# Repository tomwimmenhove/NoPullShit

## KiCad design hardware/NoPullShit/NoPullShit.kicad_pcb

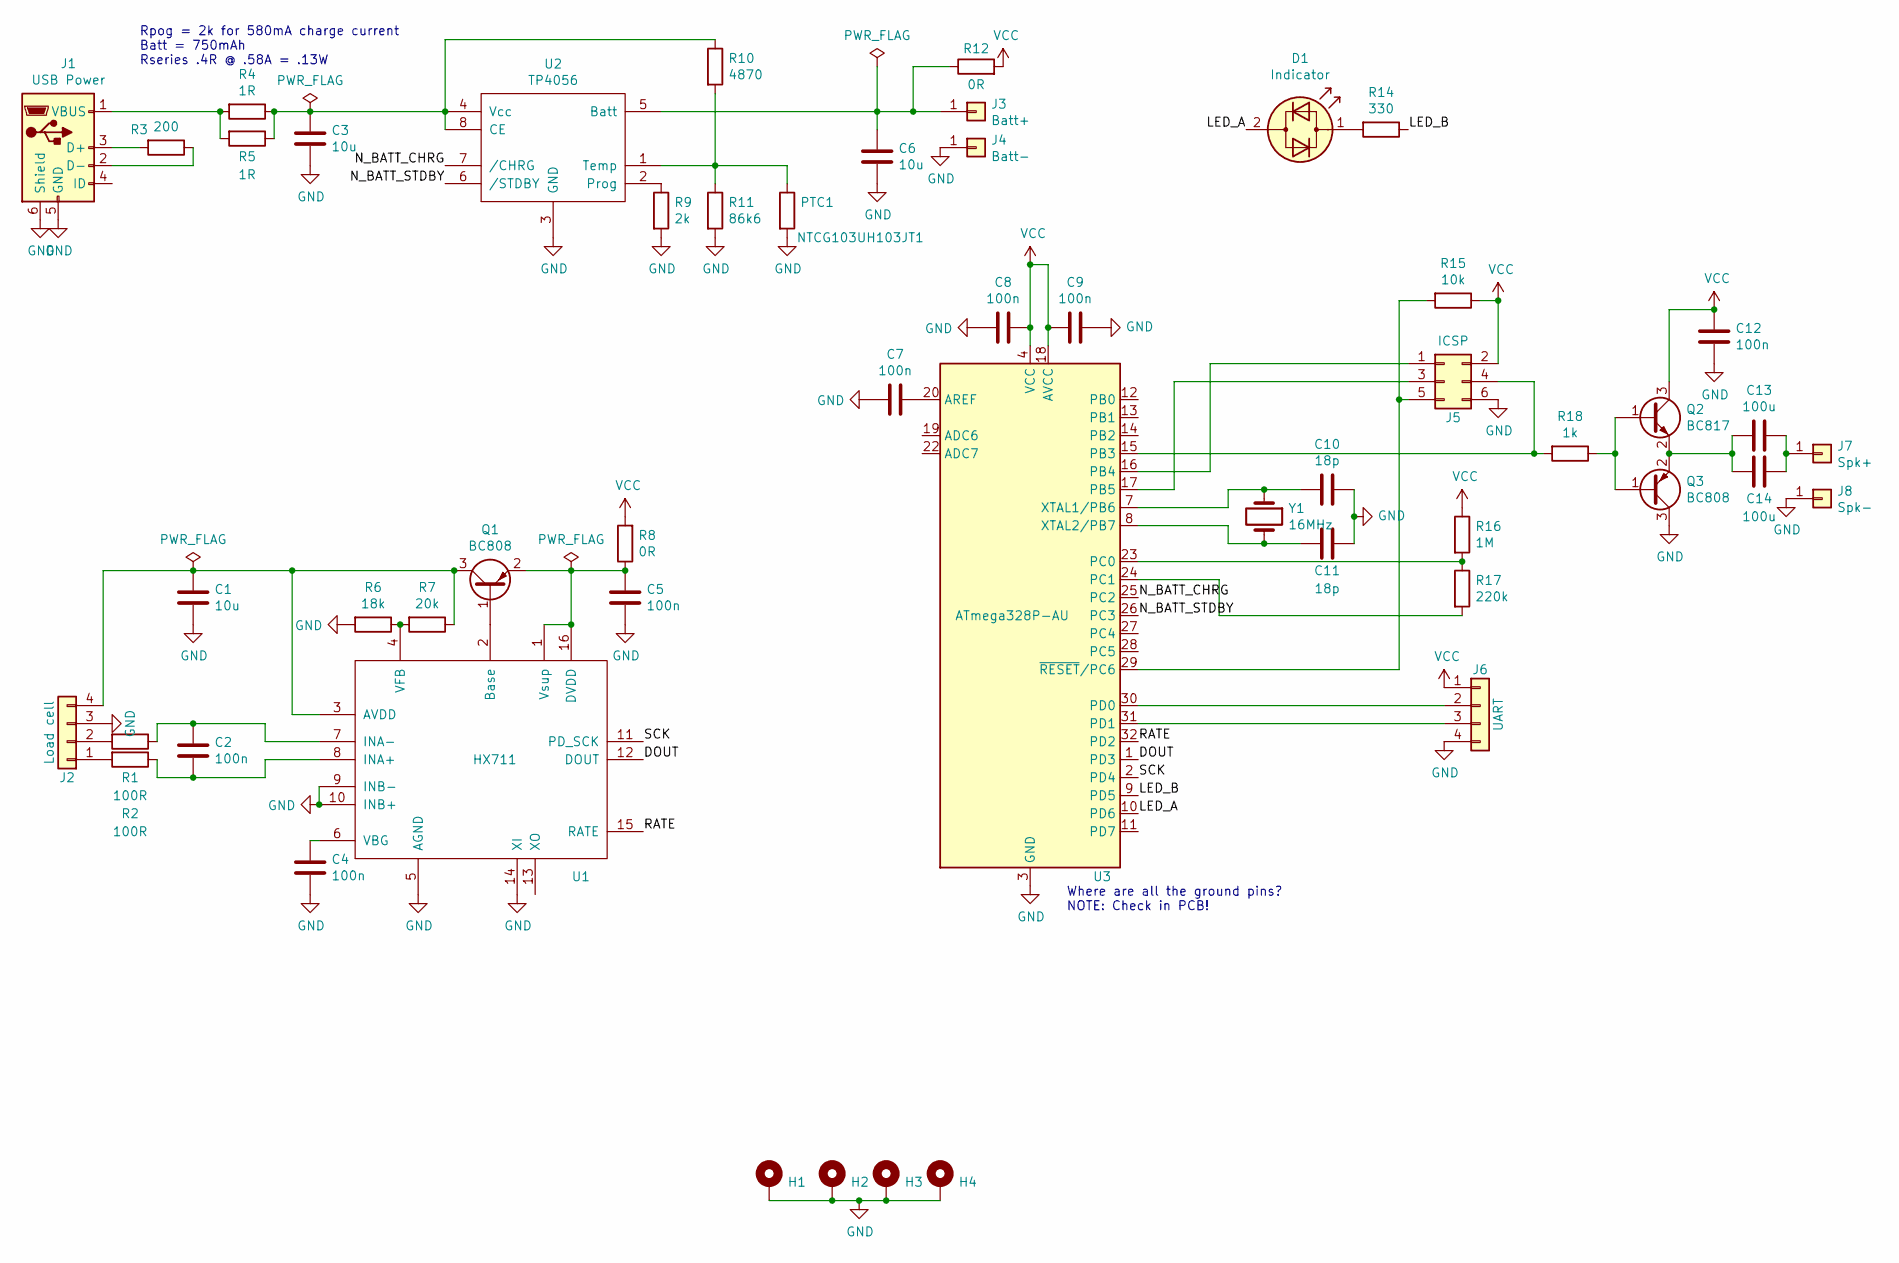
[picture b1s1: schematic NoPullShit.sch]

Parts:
C1, C3, C6: 10u; C_0805_2012Metric
C2, C4, C5, C7, C8, C9, C12: 100n; C_0603_1608Metric
C10, C11: 18p; C_0603_1608Metric
C13, C14: 100u; C_1206_3216Metric
D1: Indicator; LED_0603_1608Metric
H1, H2, H3, H4: MountingHole_Pad; MountingHole_2.2mm_M2_Pad_Via
J1: USB Power; USB_Micro-B_Amphenol_10103594-0001LF_Horizontal
J2: Load cell; PinHeader_1x04_P2.00mm_Vertical
J3: Batt+; TestPoint_THTPad_1.0x1.0mm_Drill0.5mm
J4: Batt-; TestPoint_THTPad_1.0x1.0mm_Drill0.5mm
J5: ICSP; PinHeader_2x03_P2.54mm_Vertical
J6: UART; PinHeader_1x04_P2.54mm_Vertical
J7: Spk+; TestPoint_THTPad_1.0x1.0mm_Drill0.5mm
J8: Spk-; TestPoint_THTPad_1.0x1.0mm_Drill0.5mm
PTC1: NTCG103UH103JT1; R_0603_1608Metric
Q1, Q3: BC808; SOT-23
Q2: BC817; SOT-23
R1, R2: 100R; R_0603_1608Metric
R3: 200; R_0603_1608Metric
R4, R5: 1R; R_0603_1608Metric
R6: 18k; R_0603_1608Metric
R7: 20k; R_0603_1608Metric
R8, R12: 0R; R_0603_1608Metric
R9: 2k; R_0603_1608Metric
R10: 4870; R_0603_1608Metric
R11: 86k6; R_0603_1608Metric
R14: 330; R_0603_1608Metric
R15: 10k; R_0603_1608Metric
R16: 1M; R_0603_1608Metric
R17: 220k; R_0603_1608Metric
R18: 1k; R_0603_1608Metric
U1: HX711; SOP-16_3.9x9.9mm_P1.27mm
U2: TP4056; SOP-8_3.9x4.9mm_P1.27mm
U3: ATmega328P-AU; TQFP-32_7x7mm_P0.8mm
Y1: 16MHz; Crystal_SMD_ECS_CSM3X-2Pin_7.6x4.1mm

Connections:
/DOUT: U1.12 (DOUT), U3.1 (PD3)
/LED_A: D1.2 (AK), U3.10 (PD6)
/LED_B: R14.1, U3.9 (PD5)
/N_BATT_CHRG: U2.7 (/CHRG), U3.25 (PC2)
/N_BATT_STDBY: U2.6 (/STDBY), U3.26 (PC3)
/RATE: U1.15 (RATE), U3.32 (PD2)
/SCK: U1.11 (PD_SCK), U3.2 (PD4)
GND: C1.2, C3.2, C4.1, C5.1, C6.2, C7.2, C8.2, C9.1, C10.1, C11.1, C12.1, H1.1, H2.1, H3.1, H4.1, J1.5 (GND), J1.6 (Shield), J2.3, J4.1, J5.6, J6.4, J8.1, PTC1.2, Q3.3 (C), R6.2, R9.2, R11.2, U1.5 (AGND), U1.9 (INB-), U1.10 (INB+), U1.14 (XI), U2.3 (GND), U3.3 (GND), U3.5 (GND), U3.21 (GND)
unnamed: C1.1, J2.4, Q1.3 (C), R7.1, U1.3 (AVDD)
unnamed: C2.1, R2.1, U1.8 (INA+)
unnamed: C2.2, R1.1, U1.7 (INA-)
unnamed: C3.1, R4.1, R5.1, R10.1, U2.4 (Vcc), U2.8 (CE)
unnamed: C4.2, U1.6 (VBG)
unnamed: C5.2, Q1.2 (E), R8.1, U1.1 (Vsup), U1.16 (DVDD)
unnamed: C6.1, J3.1, R12.1, U2.5 (Batt)
unnamed: C7.1, U3.20 (AREF)
unnamed: C10.2, U3.7 (XTAL1/PB6), Y1.1
unnamed: C11.2, U3.8 (XTAL2/PB7), Y1.2
unnamed: C13.1, C14.1, J7.1
unnamed: C13.2, C14.2, Q2.2 (E), Q3.2 (E)
unnamed: D1.1 (KA), R14.2
unnamed: J1.1 (VBUS), R4.2, R5.2
unnamed: J1.2 (D-), R3.1
unnamed: J1.3 (D+), R3.2
unnamed: J2.1, R2.2
unnamed: J2.2, R1.2
unnamed: J5.1, U3.16 (PB4)
unnamed: J5.3, U3.17 (PB5)
unnamed: J5.4, R18.2, U3.15 (PB3)
unnamed: J5.5, R15.2, U3.29 (~RESET~/PC6)
unnamed: J6.2, U3.30 (PD0)
unnamed: J6.3, U3.31 (PD1)
unnamed: PTC1.1, R10.2, R11.1, U2.1 (Temp)
unnamed: Q1.1 (B), U1.2 (Base)
unnamed: Q2.1 (B), Q3.1 (B), R18.1
unnamed: R6.1, R7.2, U1.4 (VFB)
unnamed: R9.1, U2.2 (Prog)
unnamed: R16.2, R17.1, U3.23 (PC0)
unnamed: R17.2, U3.24 (PC1)
VCC: C8.1, C9.2, C12.2, J5.2, J6.1, Q2.3 (C), R8.2, R12.2, R15.1, R16.1, U3.4 (VCC), U3.6 (VCC), U3.18 (AVCC)

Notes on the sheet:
Rpog = 2k for 580mA charge current Batt = 750mAh Rseries .4R @ .58A = .13W
Where are all the ground pins? NOTE: Check in PCB!

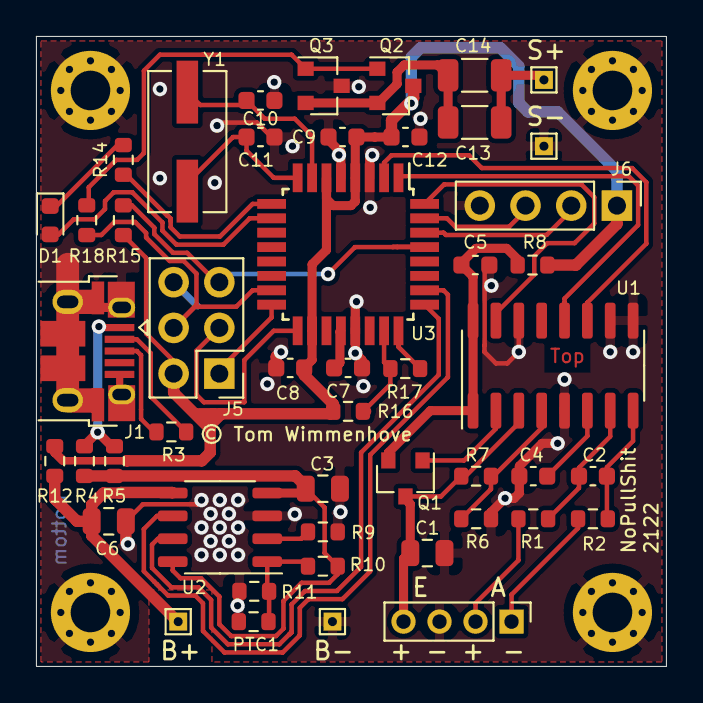
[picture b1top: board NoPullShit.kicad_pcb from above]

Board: 2 copper layers, 35.0 x 35.0 mm, 52 parts (0 on the bottom side), 40 nets.

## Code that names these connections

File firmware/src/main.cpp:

/*
 * main.cpp
 *
 *  Created on: Jun 14, 2021
 *      Author: Tom Wimmenhove
 */

#include <avr/sleep.h>
#include <avr/interrupt.h>
#include <util/delay.h>
#include <avr/eeprom.h>

#include "config.h"
#include "audio.h"
#include "hx711.h"
#include "waves.h"
#include "standby.h"
#include "battery.h"
#include "watchdog.h"
#ifdef DEBUG
#	include "serial.h"
#endif

static int32_t baseline = 0;

static hx711 scale(&DOUT_PIN, DOUT_MASK, &SCK_PORT, SCK_MASK, &RATE_PORT, RATE_MASK);
static standby stdby;

void update_baseline(int32_t& value)
{
#	ifdef DEBUG
	serial::puts("Updating baseline: ");
	serial::puti(value + baseline);
	serial::putc('\n');
	serial::flush();
#	endif
	baseline = value + baseline;
	value = 0;
}

uint8_t calculate_volume(int32_t value, int32_t threshold)
{
	int32_t volume = MIN_VOLUME + (255 - MIN_VOLUME) * (value - threshold) / (threshold * MAX_OVERPULL / 256);
	if (volume < MIN_VOLUME)
	{
		return MIN_VOLUME;
	}
	else if (volume > 255)
	{
		return 255;
	}

	return volume;
}

enum e_main_state
{
	standby,
	normal,
	wait_for_depress,
	wait_for_press,
	config
};

void led_off()
{
	LEDA_PORT &= ~LEDA_MASK;
	LEDB_PORT &= ~LEDB_MASK;
}

void led_on(bool red)
{
	if (red)
	{
		LEDA_PORT |= LEDA_MASK;
		LEDB_PORT &= ~LEDB_MASK;
	}
	else
	{
		LEDA_PORT &= ~LEDA_MASK;
		LEDB_PORT |= LEDB_MASK;
	}
}

int main()
{
	e_main_state mainstate = e_main_state::standby;
	int32_t last_value = 0;
	int32_t new_pull_threshold;
	uint16_t blink_timer = 0;
	int32_t pull_threshold = MIN_PULL_FORCE;
	int8_t alert_count = 0;
	int16_t config_timer = 0;
	int16_t alert_timer = 0;
	int16_t update_baseline_timer = 0;

	// set everything unused to outputs
	DDRB = 0xff &
			~(1 << 3);  // PB3 is PWM out;
	DDRC = 0xff &
			~(1 << 0) & // ADC0 is batt monitor
			~(1 << 2) & // PC2 = CHRG
			~(1 << 3);  // PC3 = STDBY
	DDRD = 0xff &
			~(1 << 0) & // PD0 = RX
			~(1 << 3);  // PD3 is DOUT

	//PORTD |= (1 << 1); // TX
	PORTD &= ~(1 << 1); // TX
	BATT_PLDWN_PORT |= BATT_PLDWN_MASK; // Batt monitor disable

#	ifdef DEBUG
	serial::init();
	serial::puts("Reset\n");
	serial::flush();
#	endif

	// Read the configured force from the EEPROM
	int32_t f = eeprom_read_dword((const uint32_t*) EE_FORCE_ADDRESS);
	if (f != -1)
	{
		pull_threshold = f;
	}

	SCK_PORT &= ~SCK_MASK;  // Set SCK low to initiate conversion
	scale.set_rate(true); // 80Hz

	EICRA |= (1 << ISC11);	// INT1 on falling edge of DOUT
	EIMSK |= (1 << INT1);	// Turns on INT1

	// Disable ADC
	ADCSRA &= ~(1 << 7);

	audio::init();

	watchdog::set((1 << WDP2)  | (1 << WDP0) | (1 << WDP1)); // 1 second

	// Make sure there's at least one transition (DOUT falling) to get shit going
	baseline = scale.read();

	// Main loop
	for(;;)
	{
		// Go to sleep, unless we're currently beeping. We will wake up when DOUT goes low. This means a conversion is ready.
		if (!audio::is_enabled())
		{
			watchdog::deep_sleep();
		}

		wdt_reset();

		battery::check(mainstate == e_main_state::standby, [] () { scale.sleep(); } );

		if (mainstate == e_main_state::standby)
		{
			if (!audio::is_enabled())
			{
				scale.wake_up();
				watchdog::deep_sleep();
			}
		}

		int32_t value = scale.read() - baseline;

		// Main state machine
		switch(mainstate)
		{
		case e_main_state::standby:
			// Go away; I'm sleeping
			break;

		case e_main_state::normal:
			// Check if the dog started or stopped pulling
			if (!audio::is_enabled())
			{
				if (value > pull_threshold + HIST_FORCE)
				{
					audio::set_volume(calculate_volume(value, pull_threshold));
					audio::play(BEEP_WAVE, sizeof(BEEP_WAVE));
				}
			}
			else
			{
				if (value < pull_threshold - HIST_FORCE)
				{
					audio::disable();
				}
				else
				{
					audio::set_volume(calculate_volume(value, pull_threshold));
				}
			}

			// Check if the user pressed the load cell
			if (value < REVERSE_FORCE - HIST_FORCE)
			{
				audio::alert(20);
				mainstate = e_main_state::wait_for_depress;
				alert_count = 0;
			}

			break;

		case e_main_state::wait_for_depress:
			// Wait until the user releases the load cell
			if (value > REVERSE_FORCE + HIST_FORCE)
			{
				mainstate = e_main_state::wait_for_press;
				alert_timer = ALERT_TIMEOUT;
			}

			break;

		case e_main_state::wait_for_press:
			// Wait for the user to press the load cell again
			if (value < REVERSE_FORCE - HIST_FORCE)
			{
				alert_count++;

				// After being pressed 3 times quickly
				if (alert_count == 2)
				{
					// 3 quick beeps
					audio::alert(20);
					_delay_ms(100);
					audio::alert(20);
					_delay_ms(100);
					audio::alert(20);

					// And go to config mode
					config_timer = 0;
					new_pull_threshold = MIN_PULL_FORCE;

					mainstate = e_main_state::config;

					break;
				}

				audio::alert(20);
				mainstate = e_main_state::wait_for_depress;
			}
			else
			{
				alert_timer--;
				if (alert_timer == 0)
				{
					mainstate = e_main_state::normal;
				}
			}
			break;

		case e_main_state::config:
			/* Use the maximum force within the configuration period */
			if (value > new_pull_threshold)
			{
				new_pull_threshold = value;
			}

			config_timer++;

#ifdef		CONFIG_BEEP_TIME
			if (config_timer % CONFIG_BEEP_TIME == 0)
			{
				audio::alert(5);
			}
#endif

			// Until we're out of time...
			if (config_timer >= CONFIG_TIME)
			{
#ifndef			CONFIG_BEEP_TIME
				audio::alert(200);
				_delay_ms(100);
				audio::alert(200);
				_delay_ms(100);
#endif

				mainstate = e_main_state::normal;

				break;
			}

			// ...or the user stopped it by pressing again
			if (value < REVERSE_FORCE - HIST_FORCE)
			{
				if (new_pull_threshold > MIN_PULL_FORCE)
				{
					pull_threshold = new_pull_threshold;

					// Let the user know the new the new settings is saved
					audio::alert(20);
					_delay_ms(100);
					audio::alert(20);
					_delay_ms(100);
					audio::alert(20);

					// Save the configured value in EEPROM
					eeprom_write_dword((uint32_t*) EE_FORCE_ADDRESS, pull_threshold);
				}
				else
				{
					audio::alert(200);
					_delay_ms(100);
					audio::alert(200);
					_delay_ms(100);
				}

				mainstate = e_main_state::normal;
			}

			break;
		}

		bool standby = stdby.check(value, last_value);

		// We entered stand by mode
		if (mainstate != e_main_state::standby && standby)
		{
#			ifdef DEBUG
			serial::puts("Going to standby\n");
			serial::flush();
#			endif

#			ifndef ALWAYS_80HZ
			scale.set_rate(true); // 80Hz rate (50ms settling time, saves mucho power)
#			endif
#			ifdef UPDATE_BASELINE_ON_STANDBY
			update_baseline(value);
#			endif
			audio::disable();

			led_off();
			blink_timer = 0;

			mainstate = e_main_state::standby;
		}

		// We returned from stand by mode
		if (mainstate == e_main_state::standby && !standby)
		{
#			ifdef DEBUG
			serial::puts("Activity! Waking up from standby\n");
			serial::flush();
#			endif

#			ifndef ALWAYS_80HZ
			scale.set_rate(false); // 10Hz default rate
#			endif

			mainstate = e_main_state::normal;
		}

		if (battery::is_standby())
		{
			led_on(false);
		}
		else if (battery::is_charging())
		{
			led_on(true);
		}
		else
		{
			led_off();
		}

		if (mainstate == e_main_state::standby)
		{
			scale.sleep();

			if (update_baseline_timer++ >= UPDATE_BASELINE_AFTER)
			{
				update_baseline_timer = 0;
				update_baseline(value);
			}
		}
		else
		{
			update_baseline_timer = 0;

			if (!battery::is_standby() && !battery::is_charging())
			{
				if (blink_timer < BLINK_TIME)
				{
					led_on(battery::is_dying());
				}
				else
				{
					led_off();
				}
			}

			if (blink_timer >= BLINK_INTERVAL)
			{      
				blink_timer = 0;
			}
			else
			{
				blink_timer++;      
			}
		}

		last_value = value;
	}
	return 0;
}

/* DOUT going low vector */
ISR (INT1_vect) { }

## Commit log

2021-05-27 Added speaker. Power saving. Standby. Etc
2021-05-27 Cleanup + Don't go to standby during beep.
2021-05-27 Removed 'DC clicks' from audio. + Option to always set 80HZ measuring rate
2021-05-27 Select differnt audio waveforms
2021-05-27 Better power saving in standby mode
2021-05-28 Configurable push force
2021-05-28 Cleanup
2021-05-28 Separated waves
2021-05-28 Removed unused macro
2021-05-28 Disable interrupts while disabling BOD
2021-05-29 Fixed small power-drain bugs
2021-05-29 Moved alert wave
2021-05-29 Better way to turn off PWM
2021-05-29 Added hysteresis
2021-05-29 Continuous update of baseline
2021-05-29 Allow stanby during beep + cleanup
2021-05-29 Added battery monitoring
2021-05-30 Cheaper battery measurement
2021-05-30 Added power/lo-batt LED
2021-05-30 Separated standby shit
2021-05-30 Minor rearrangement
2021-06-01 Added KiCad hardware project
2021-06-02 Footprint assignment + initial grouping
2021-06-02 Initial routing backup
2021-06-02 Finished initla routing
2021-06-02 Fixed RefDes placement
2021-06-03 Small layout changes
2021-06-03 Repinning
2021-06-04 Small small changes
2021-06-05 More smaller, more better
2021-06-05 Tiny optimizations
2021-06-06 Neatify
2021-06-06 PSU current sense fix + some shuffling
2021-06-06 Better ground around x-tal
2021-06-06 Slightly improved ground-plane
2021-06-08 Hopefully ready for JLCPCB
2021-06-09 Converted to stand-alone Makefile project
2021-06-09 Added "all" target to Makefile
2021-06-09 Added eclipse project
2021-06-10 Moved globals to main()
2021-06-10 Cleaned up state-machine
2021-06-11 Added variable volume depending on pull force
2021-06-11 Removed eclipse project. Added gitignore
2021-06-12 I can haz bad math
2021-06-12 I can haz bad spellingz
2021-06-12 Manually stop config mode
2021-06-12 Minor audio cleanup and reset OCR2A when disabling audio
2021-06-12 Don't compile serial when not DEBUG
2021-06-14 A little more obsessive separating
2021-06-14 Added headers
2021-06-15 scale.sleep() as lambda
2021-06-16 Small Makefile improvement
2021-06-19 Added CAD models for PCB, Load cell, Battery and Speaker
2021-06-20 Freecad backup
2021-06-20 Finished initial draft of case
2021-06-20 Added screw supports and holes
2021-06-20 Backup before FreeCAD fuckup
2021-06-21 Fixed some chamfers/fillets and combined parts
2021-06-21 Added STLs
2021-06-21 Fillet load cell
2021-06-21 Added battery drawing
2021-06-22 Fixed some normals
2021-06-22 backup
2021-06-23 Added LED behind 200um window
2021-06-23 Shit's round now!
2021-06-23 Forgot to add bottom section without holes
2021-06-24 Production config
2021-06-24 Added charger indicators
2021-06-24 Changed screw placement and reinforced them
2021-06-24 Added SLA STLs
2021-06-24 Backup before cleanup
2021-06-24 Removed tons of old shit
2021-06-24 Fixed screw hole size
2021-06-24 Also fixed screw hole size for PCB
2021-06-24 Inverted ridges
2021-06-26 Started from the wrong fucking branch. Fuck this
2021-06-29 It's smaller now.
2021-06-30 'Twas too tight

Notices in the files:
hardware/NoPullShit/NoPullShit.kicad_pcb:
© Tom Wimmenhove
